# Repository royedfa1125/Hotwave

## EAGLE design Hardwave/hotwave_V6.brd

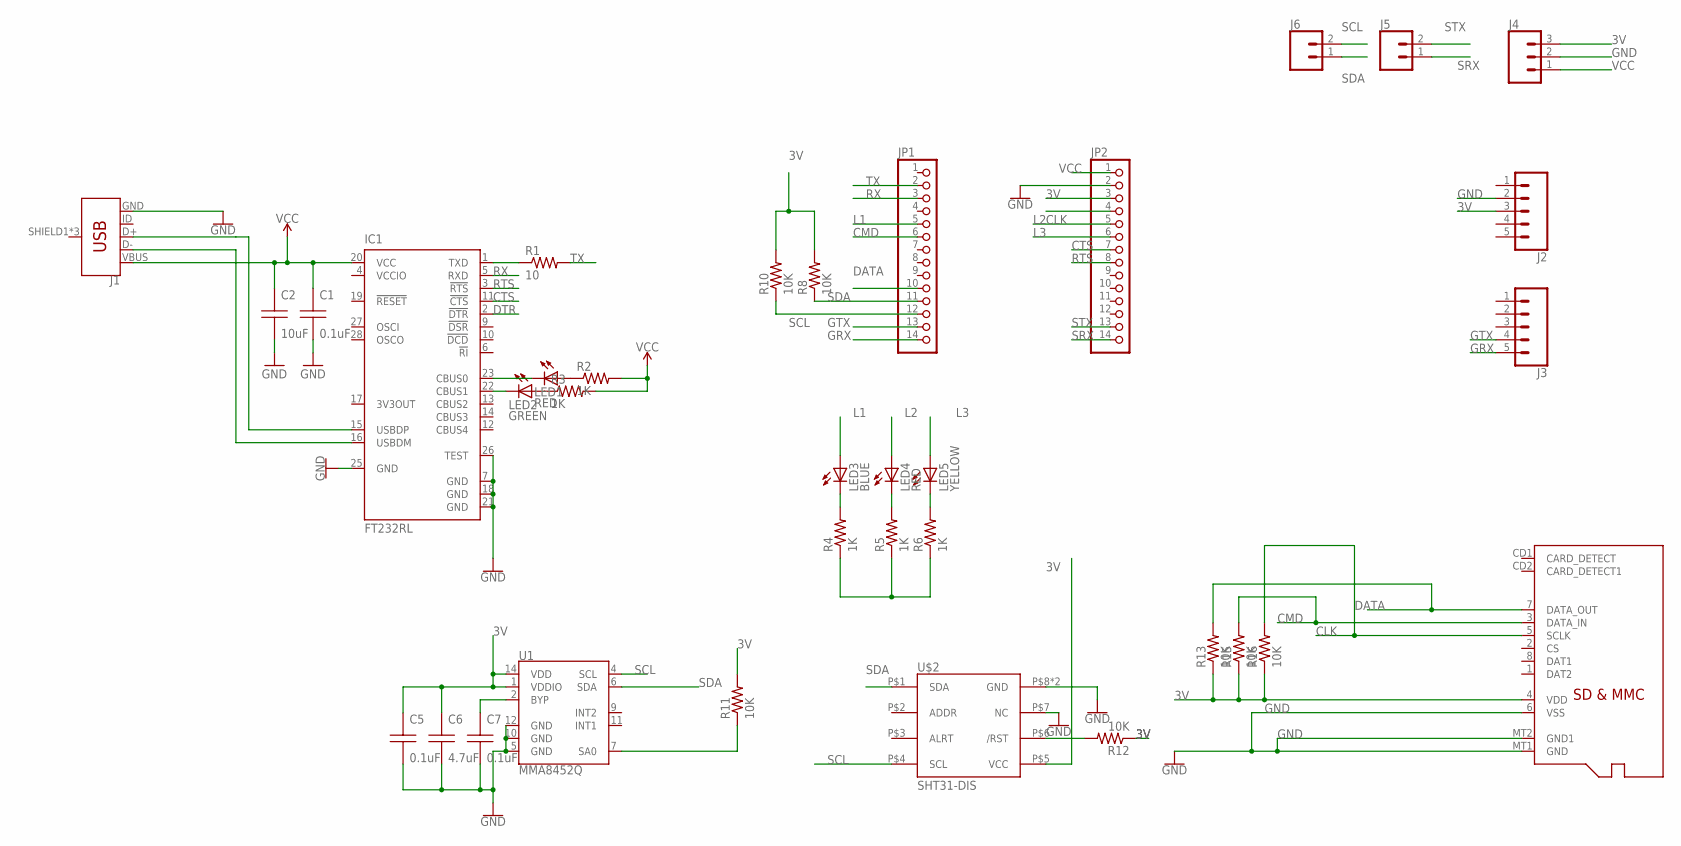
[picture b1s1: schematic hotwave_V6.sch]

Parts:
C1, C5, C7: 0.1uF; C0805
C2: 10uF; C0805
C6: 4.7uF; C0805
IC1: FT232RL; SSOP28
J1: USB_MICRO-B_FEMALE-SMT; USB-B-MICRO-SMD
J2, J3: CONN_05; 1X05
J4: CONN_03; 1X03
J5, J6: CONN_02; 1X02
JP1, JP2: PINHD-1X14-CB; 1X14-CB
LED1, LED4: RED; SML0805
LED2: GREEN; SML0805
LED3: BLUE; SML0805
LED5: YELLOW; SML0805
R1: 10; R0805
R2, R3, R4, R5, R6: 1K; R0805
R8, R10, R11, R12, R13, R15, R16: 10K; R0805
U1: MMA8452Q; QFN-16
U$1: MICROSD
U$2: SHT31-DIS; SHT3X

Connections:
3V: C5.1 (A), C6.1 (A), J2.3, J4.3, JP2.3, R8.2, R10.2, R11.2, R12.1, R13.1, R15.1, R16.1, U1.1 (VDDIO), U1.14 (VDD), U$1.4 (VDD), U$2.P$5 (VCC)
CLK: JP2.4, R16.2, U$1.5 (SCLK)
CMD: JP1.6, R15.2, U$1.3 (DATA_IN)
CTS: IC1.11 (!CTS), JP2.7
DATA: JP1.10, R13.2, U$1.7 (DATA_OUT)
DTR: IC1.2 (!DTR)
GND: C1.2 (B), C2.2 (B), C5.2 (B), C6.2 (B), C7.2 (B), IC1.7 (GND), IC1.18 (GND), IC1.21 (GND), IC1.25 (GND), IC1.26 (TEST), J1.GND, J2.2, J4.2, JP2.2, R4.1, R5.1, R6.1, U1.5 (GND), U1.10 (GND), U1.12 (GND), U$1.6 (VSS), U$1.MT1 (GND), U$1.MT2 (GND1), U$2.P$7 (NC), U$2.P$8 (GND), U$2.PAD (GND)
GRX: J3.5, JP1.14
GTX: J3.4, JP1.13
L1: JP1.5, LED3.A
L2: JP2.5, LED4.A
L3: JP2.6, LED5.A
unnamed: IC1.15 (USBDP), J1.D+
unnamed: IC1.16 (USBDM), J1.D-
unnamed: IC1.1 (TXD), R1.1
unnamed: LED1.A, R2.1
unnamed: LED2.A, R3.1
unnamed: IC1.23 (CBUS0), LED1.C
unnamed: IC1.22 (CBUS1), LED2.C
unnamed: R11.1, U1.7 (SA0)
unnamed: C7.1 (A), U1.2 (BYP)
unnamed: LED3.C, R4.2
unnamed: R12.2, U$2.P$6 (/RST)
unnamed: LED4.C, R5.2
unnamed: LED5.C, R6.2
RTS: IC1.3 (!RTS), JP2.8
RX: IC1.5 (RXD), JP1.3
SCL: J6.2, JP1.12, R10.1, U1.4 (SCL), U$2.P$4 (SCL)
SDA: J6.1, JP1.11, R8.1, U1.6 (SDA), U$2.P$1 (SDA)
SRX: J5.1, JP2.14
STX: J5.2, JP2.13
TX: JP1.2, R1.2
VCC: C1.1 (A), C2.1 (A), IC1.20 (VCC), J1.VBUS, J4.1, JP2.1, R2.2, R3.2
VCCIO: IC1.4 (VCCIO)

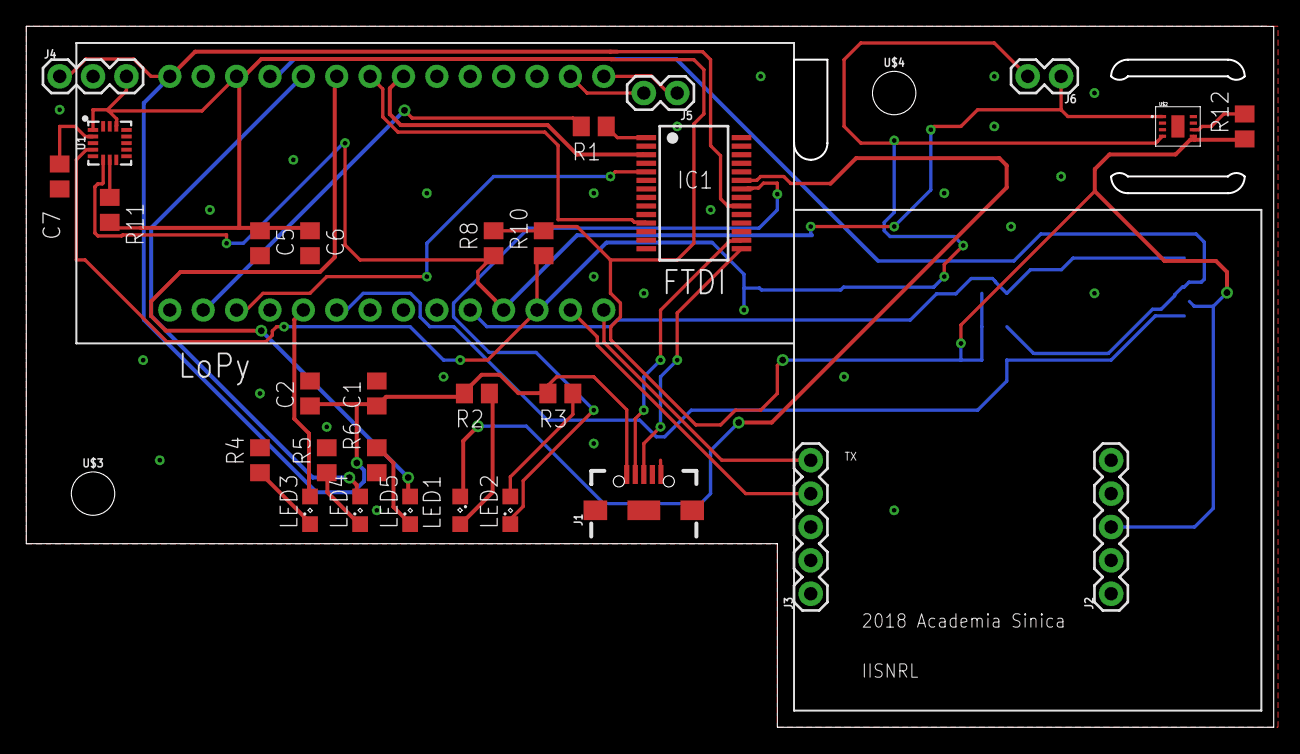
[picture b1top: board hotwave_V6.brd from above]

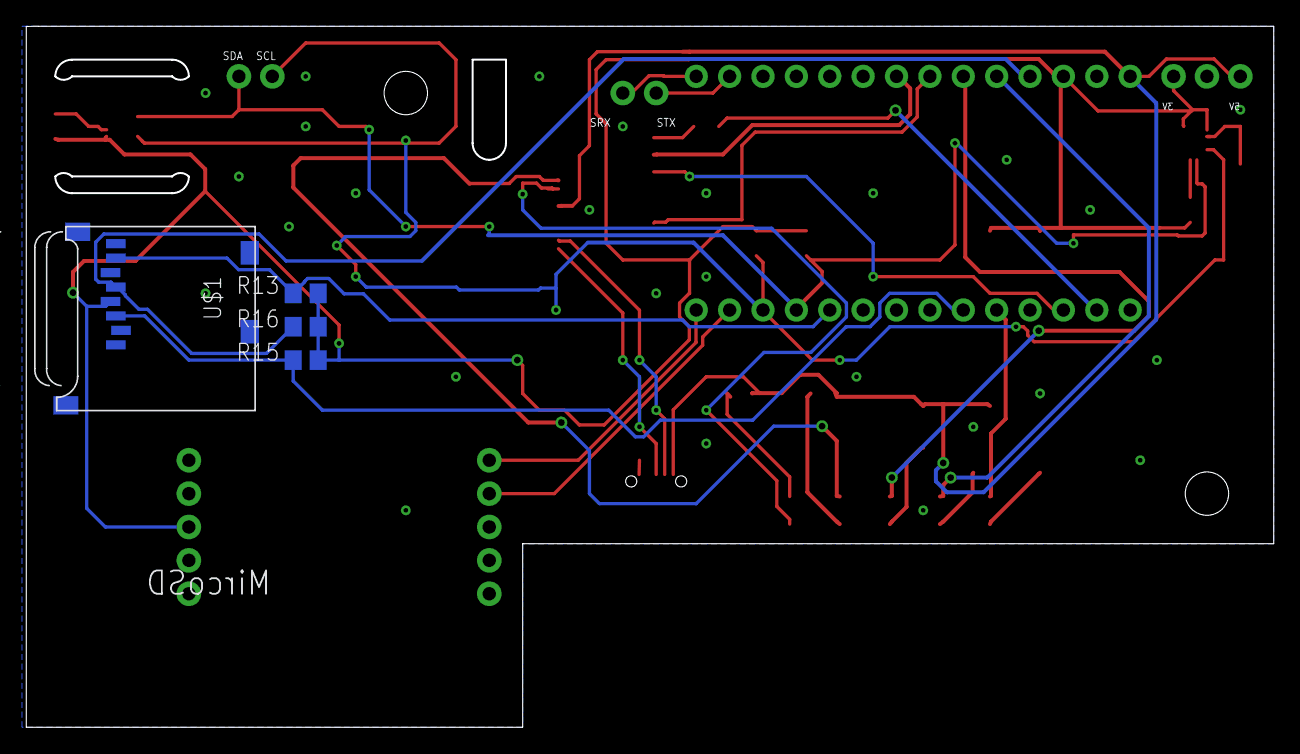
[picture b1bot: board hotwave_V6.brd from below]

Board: 2 copper layers, 94.8 x 53.2 mm, 37 parts (4 on the bottom side), 32 nets.

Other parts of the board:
U$3, U$4: STAND-OFF

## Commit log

2018-07-24 PCB brd
2018-07-24 PCB sch
2018-07-29 Pycom boot.py
2018-07-29 Pycom library
2018-07-29 This project the main code

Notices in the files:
parts and their libraries:
SparkFun-Connectors: Licensing: Creative Commons ShareAlike 4.0 International - https://creativecommons.org/licenses/by-sa/4.0
